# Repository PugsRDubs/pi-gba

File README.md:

# pi-gba
A simple, easy to assemble, DIY retro gaming handheld.

The pi-gba was designed to be pretty easy to build. Order the pcb, parts, and 3d print the case, and assembly is straightforward. The pi, battery board, and usbc breakout are placed on top of and soldered directly to the main board.

### images

### software
Flash the latest image of [retropie](https://retropie.org.uk/download/) using the raspberry pi imager. Make sure SSH is enabled and ssh into the pi from another computer (instructions [here](https://retropie.org.uk/docs/SSH/)). 
I recommend installing the [fbcp-ili9341](https://github.com/juj/fbcp-ili9341) driver, clone the git repository and follow the instructions to build from source make sure to pass the flag `-DILI9488=ON` when compiling, as that is the driver that this project's screen uses. 
For keyboard controls I would use [retrogame](https://github.com/adafruit/Adafruit-Retrogame/tree/master), follow their instructions for install and then you should be able to use the `retrogame.cfg` from this repository.
Note this software has not been tested yet with this project.

| Item                    | Qty. | Price(USD) | Link                                                                                                    |
|-------------------------|------|------------|---------------------------------------------------------------------------------------------------------|
| ER-TFTM035-6            | 1    | 13.43      | https://www.buydisplay.com/lcd-3-5-inch-320x480-tft-display-module-optl-touch-screen-w-breakout-board   |
| BuyDisplay shipping     | 1    | 9.41       | N/A                                                                                                     |
| PowerBoost 1000         | 1    | 19.95      | https://www.digikey.com/en/products/detail/adafruit-industries-llc/2465/5356834                         |
| USB-C Breakout          | 1    | 2.95       | https://www.digikey.com/en/products/detail/adafruit-industries-llc/4090/9951930                         |
| TS04-66-55-BK-100-SMT   | 15   | 0.143      | https://www.digikey.com/en/products/detail/same-sky-formerly-cui-devices/TS04-66-55-BK-100-SMT/15634326 |
| LTL-307E                | 1    | 0.14       | https://www.digikey.com/en/products/detail/liteon/LTL-307E/669997                                       |
| CFM14JT100R             | 1    | 0.10       | https://www.digikey.com/en/products/detail/stackpole-electronics-inc/CFM14JT100R/1742057                |
| EG1206                  | 1    | 0.74       | https://www.digikey.com/en/products/detail/e-switch/EG1206/251333                                       |
| 2500mAh battery         | 1    | 14.95      | https://www.digikey.com/en/products/detail/e-switch/EG1206/251333                                       |
| Digikey Shipping        | 1    | 4.99       | N/A                                                                                                     |
| PCB                     | 1    | 9.00       | N/A                                                                                                     |
| JLCPCB Shipping + taxes | 1    | 39.44      | N/A                                                                                                     |
| Raspberry Pi Zero 2 W   | 1    | 19.05      | https://www.adafruit.com/product/5291                                                                   |

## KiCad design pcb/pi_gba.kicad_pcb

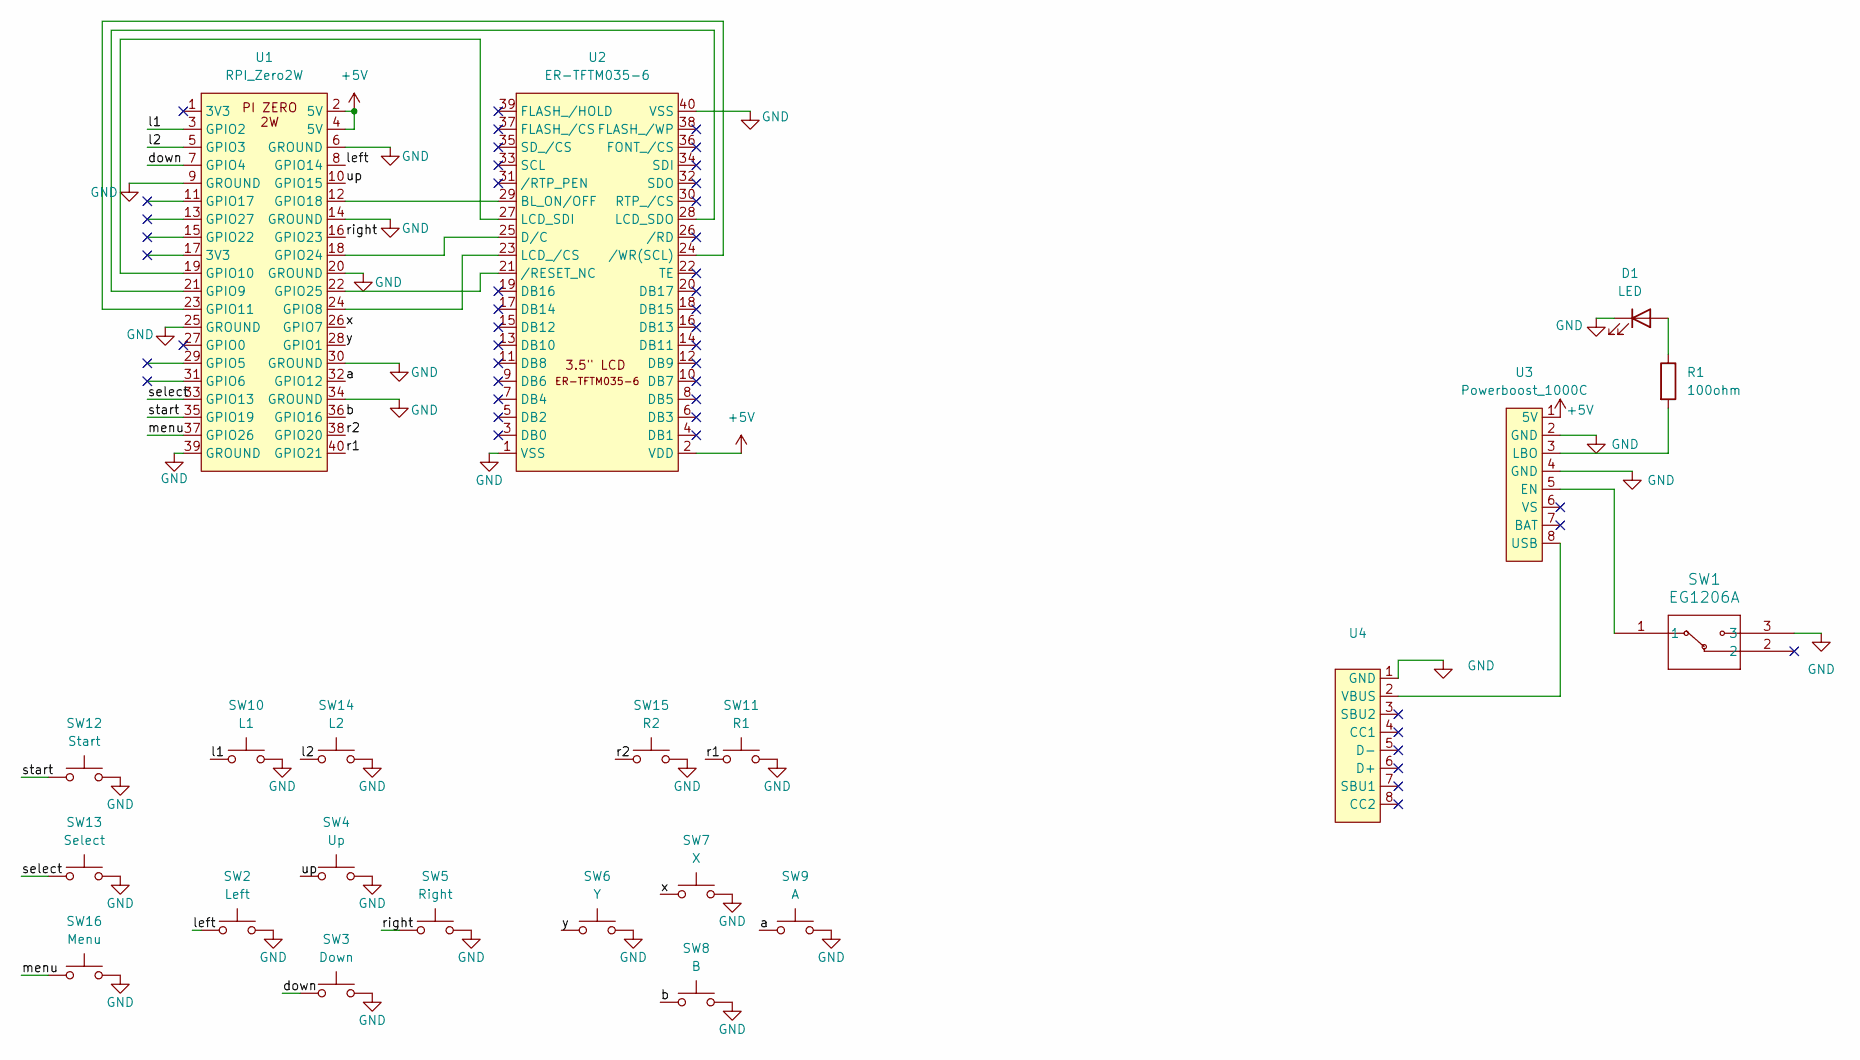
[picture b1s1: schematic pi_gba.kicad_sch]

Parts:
D1: LED; LED_D5.0mm
R1: 100ohm; R_Axial_DIN0207_L6.3mm_D2.5mm_P10.16mm_Horizontal
SW1: EG1206A; EG1206A_EWI
SW2: Left; SW_TS04-66-55-BK-100-SMT
SW3: Down; SW_TS04-66-55-BK-100-SMT
SW4: Up; SW_TS04-66-55-BK-100-SMT
SW5: Right; SW_TS04-66-55-BK-100-SMT
SW6: Y; SW_TS04-66-55-BK-100-SMT
SW7: X; SW_TS04-66-55-BK-100-SMT
SW8: B; SW_TS04-66-55-BK-100-SMT
SW9: A; SW_TS04-66-55-BK-100-SMT
SW10: L1; SW_TS04-66-55-BK-100-SMT
SW11: R1; SW_TS04-66-55-BK-100-SMT
SW12: Start; SW_TS04-66-55-BK-100-SMT
SW13: Select; SW_TS04-66-55-BK-100-SMT
SW14: L2; SW_TS04-66-55-BK-100-SMT
SW15: R2; SW_TS04-66-55-BK-100-SMT
SW16: Menu; SW_TS04-66-55-BK-100-SMT
U1: RPI_Zero2W; pi_zero_2w
U2: ER-TFTM035-6
U3: Powerboost_1000C; adafruit_powerboost_1000c
U4: adafruit_usbc_breakout

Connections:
+5V: U1.2 (5V), U1.4 (5V), U2.2 (VDD), U3.1 (5V)
/a: SW9.1, SW9.3 (1), U1.32 (GPIO12)
/b: SW8.1, SW8.3 (1), U1.36 (GPIO16)
/down: SW3.1, SW3.3 (1), U1.7 (GPIO4)
/l1: SW10.1, SW10.3 (1), U1.3 (GPIO2)
/l2: SW14.1, SW14.3 (1), U1.5 (GPIO3)
/left: SW2.1, SW2.3 (1), U1.8 (GPIO14)
/menu: SW16.1, SW16.3 (1), U1.37 (GPIO26)
/r1: SW11.1, SW11.3 (1), U1.40 (GPIO21)
/r2: SW15.1, SW15.3 (1), U1.38 (GPIO20)
/right: SW5.1, SW5.3 (1), U1.16 (GPIO23)
/select: SW13.1, SW13.3 (1), U1.33 (GPIO13)
/start: SW12.1, SW12.3 (1), U1.35 (GPIO19)
/up: SW4.1, SW4.3 (1), U1.10 (GPIO15)
/x: SW7.1, SW7.3 (1), U1.26 (GPIO7)
/y: SW6.1, SW6.3 (1), U1.28 (GPIO1)
GND: D1.1 (K), SW1.3, SW2.2, SW2.4 (2), SW3.2, SW3.4 (2), SW4.2, SW4.4 (2), SW5.2, SW5.4 (2), SW6.2, SW6.4 (2), SW7.2, SW7.4 (2), SW8.2, SW8.4 (2), SW9.2, SW9.4 (2), SW10.2, SW10.4 (2), SW11.2, SW11.4 (2), SW12.2, SW12.4 (2), SW13.2, SW13.4 (2), SW14.2, SW14.4 (2), SW15.2, SW15.4 (2), SW16.2, SW16.4 (2), U1.6 (GROUND), U1.9 (GROUND), U1.14 (GROUND), U1.20 (GROUND), U1.25 (GROUND), U1.30 (GROUND), U1.34 (GROUND), U1.39 (GROUND), U2.1 (VSS), U2.40 (VSS), U3.2 (GND), U3.4 (GND), U4.1 (GND)
unnamed: D1.2 (A), R1.1
unnamed: U1.24 (GPIO8), U2.23 (LCD_/CS)
unnamed: U1.21 (GPIO9), U2.28 (LCD_SDO)
unnamed: U1.19 (GPIO10), U2.27 (LCD_SDI)
unnamed: U1.23 (GPIO11), U2.24 (/WR(SCL))
unnamed: U1.12 (GPIO18), U2.29 (BL_ON/OFF)
unnamed: U1.18 (GPIO24), U2.25 (D/C)
unnamed: U1.22 (GPIO25), U2.21 (/RESET_NC)
unnamed: SW1.1, U3.5 (EN)
unnamed: R1.2, U3.3 (LBO)
unnamed: U3.8 (USB), U4.2 (VBUS)

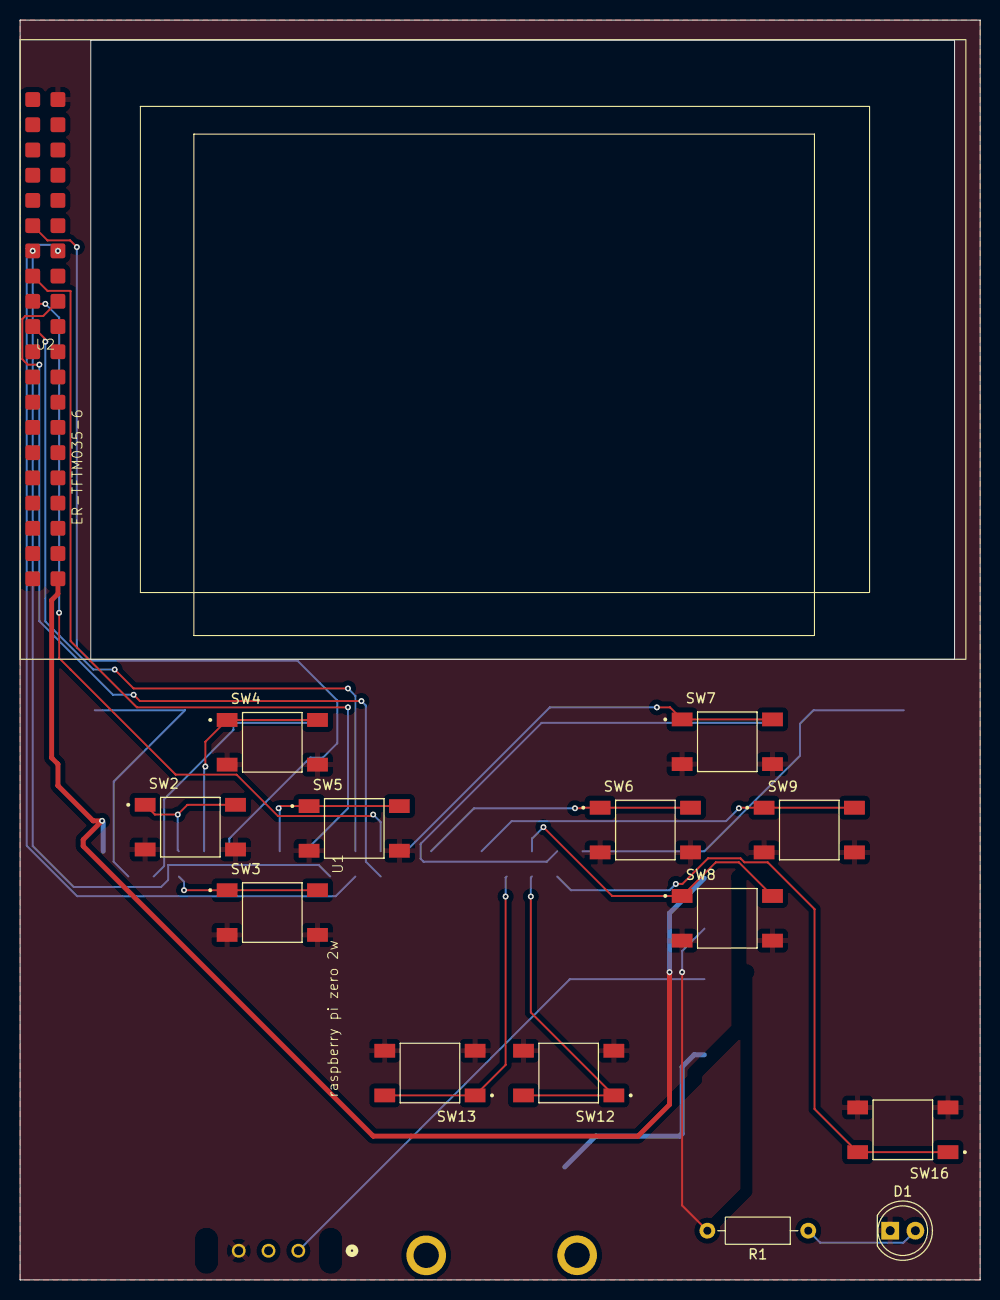
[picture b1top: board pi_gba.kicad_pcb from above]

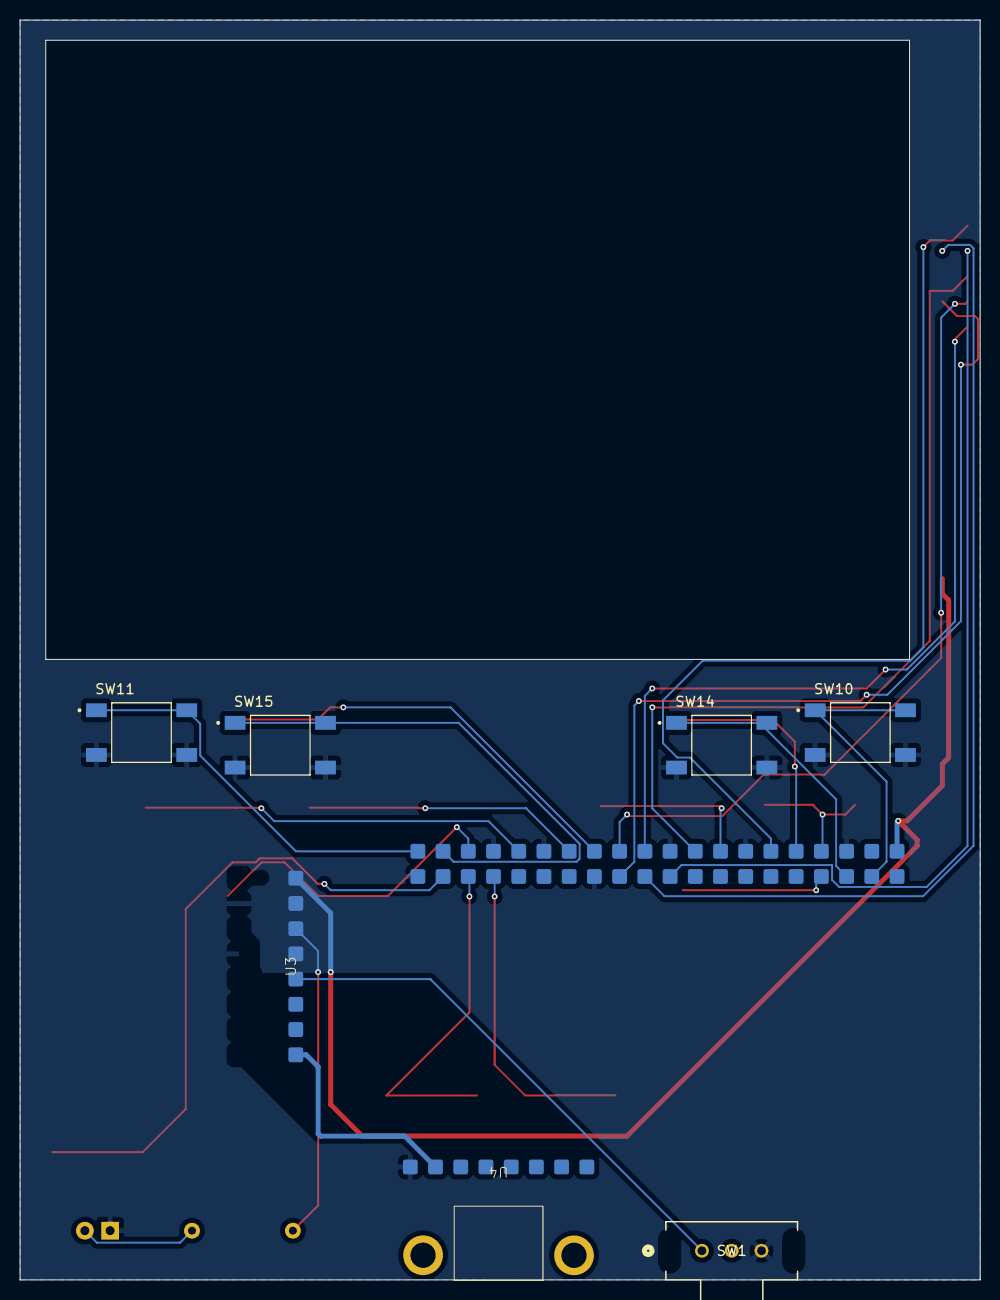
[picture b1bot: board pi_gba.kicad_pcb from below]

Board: 2 copper layers, 96.7 x 126.9 mm, 22 parts (7 on the bottom side), 28 nets.

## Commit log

2026-03-31 add project files
2026-03-31 change button
2026-03-31 add step
2026-05-04 schematic redesign
